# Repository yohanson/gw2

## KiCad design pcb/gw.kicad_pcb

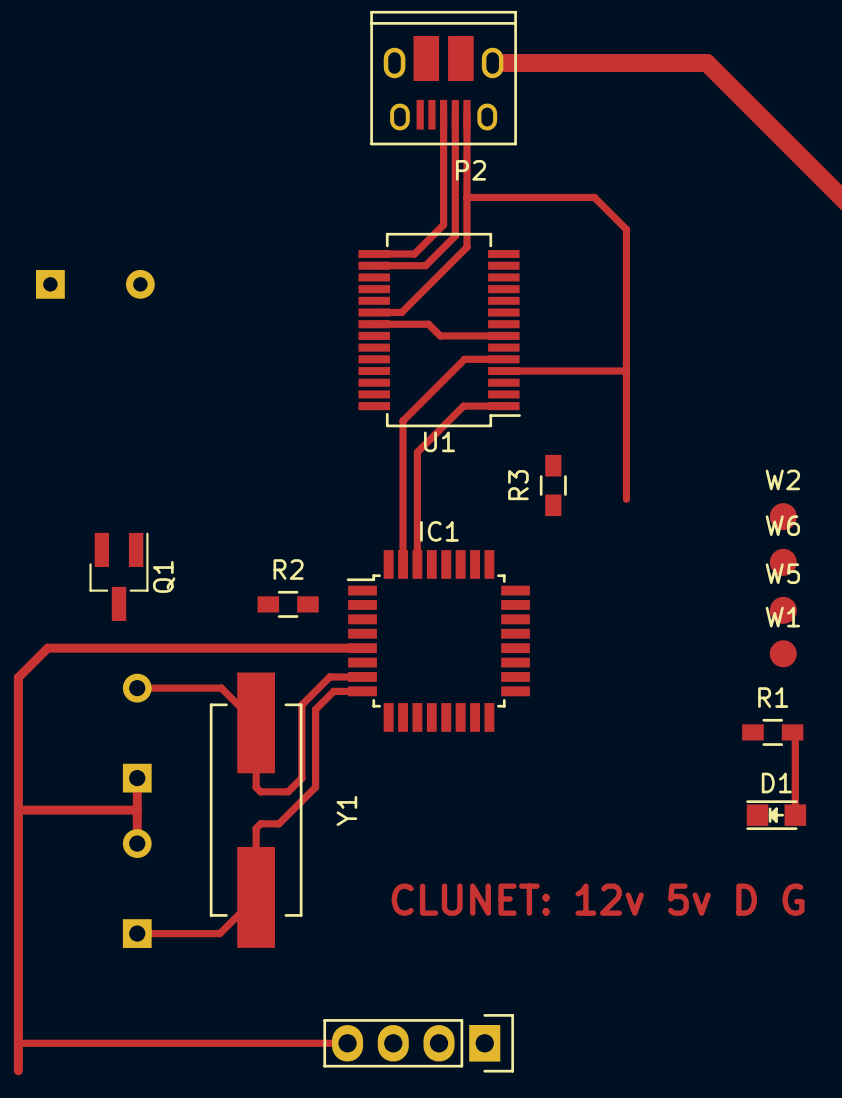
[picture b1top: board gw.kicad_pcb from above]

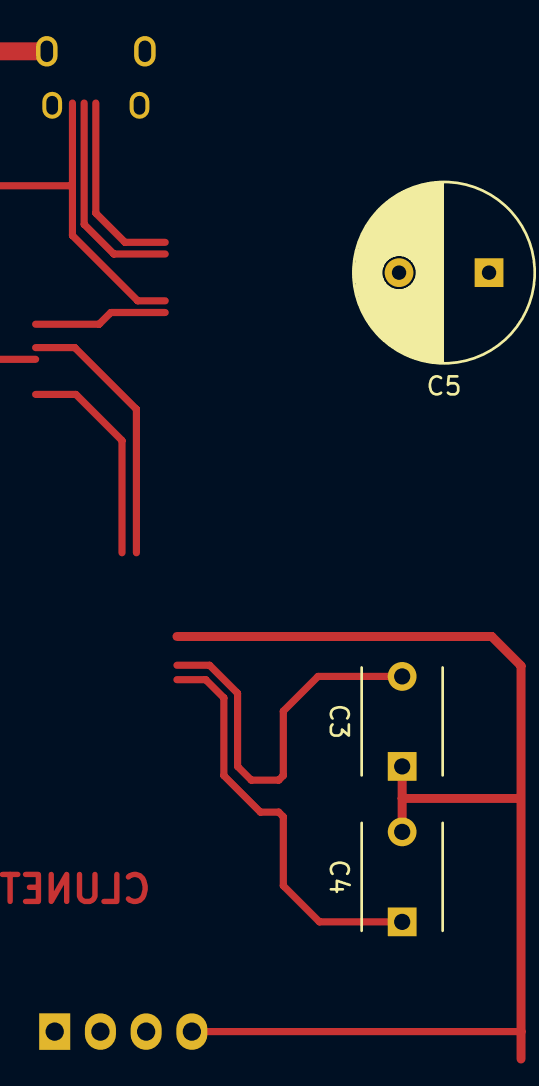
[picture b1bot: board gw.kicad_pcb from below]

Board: 2 copper layers, 17 parts (3 on the bottom side), 17 nets.

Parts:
C3, C4: C; C_Disc_D6_P5
C5: CP; C_Radial_D10_L13_P5
D1: LED; LED_0805
IC1: ATMEGA8A-P; TQFP-32_7x7mm_Pitch0.8mm
P1: CONN_CLUNET; Socket_Strip_Straight_1x04
P2: USB_OTG; USB_Micro-B_10103594-0001LF
Q1: BC849; SOT-23_Handsoldering
R1: 470; R_0603_HandSoldering
R2: 5k; R_0603_HandSoldering
R3: 2k2; R_0603_HandSoldering
U1: FT232RL; SSOP-28_5.3x10.2mm_Pitch0.65mm
W1: MOSI; Measurement_Point_Round-SMD-Pad_Small
W2: RST; Measurement_Point_Round-SMD-Pad_Small
W5: MISO; Measurement_Point_Round-SMD-Pad_Small
W6: SCK; Measurement_Point_Round-SMD-Pad_Small
Y1: Crystal; Crystal_HC49-SD_SMD

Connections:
/Clunet_IN: IC1.32, P1.3, Q1.3
/Clunet_OUT: IC1.2, R2.2
/Reset: IC1.29, R3.1, W2.1
/USBD+: P2.3, U1.15
/USBD-: P2.2, U1.16
/xtal1: C3.2, IC1.7, Y1.1
/xtal2: C4.1, IC1.8, Y1.2
GND: C3.1, C4.2, C5.2, D1.1, IC1.3, IC1.5, IC1.21, P1.4, P2.5, P2.6, Q1.2, U1.7, U1.18, U1.21, U1.25, U1.26
MISO: IC1.16, W5.1
MOSI: IC1.15, W1.1
unnamed: D1.2, R1.2
unnamed: IC1.13, R1.1
unnamed: Q1.1, R2.1
SCK: IC1.17, W6.1
UART_RX: IC1.30, U1.1
UART_TX: IC1.31, U1.5
VCC: C5.1, IC1.4, IC1.6, P1.2, P2.1, R3.2, U1.4, U1.20

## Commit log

2019-07-08 Initial
2019-07-09 Switch PCB sides, TQFP32 atmega
